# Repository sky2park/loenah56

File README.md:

# loenah56
Loenah56, A split-keyboard with 56 keys.

# How to flash firmware
Use qmk toolbox. Copy loenah folder to qmk toolbox keyboard folder.

Connect one side with bootloader mode. Execute qmk toolbox and execute below line.

qmk flash -kb loenah -km default -bl uf2-split-left (for left)

qmk flash -kb loenah -km default -bl uf2-split-right (for right)

Connect other side and do as same.

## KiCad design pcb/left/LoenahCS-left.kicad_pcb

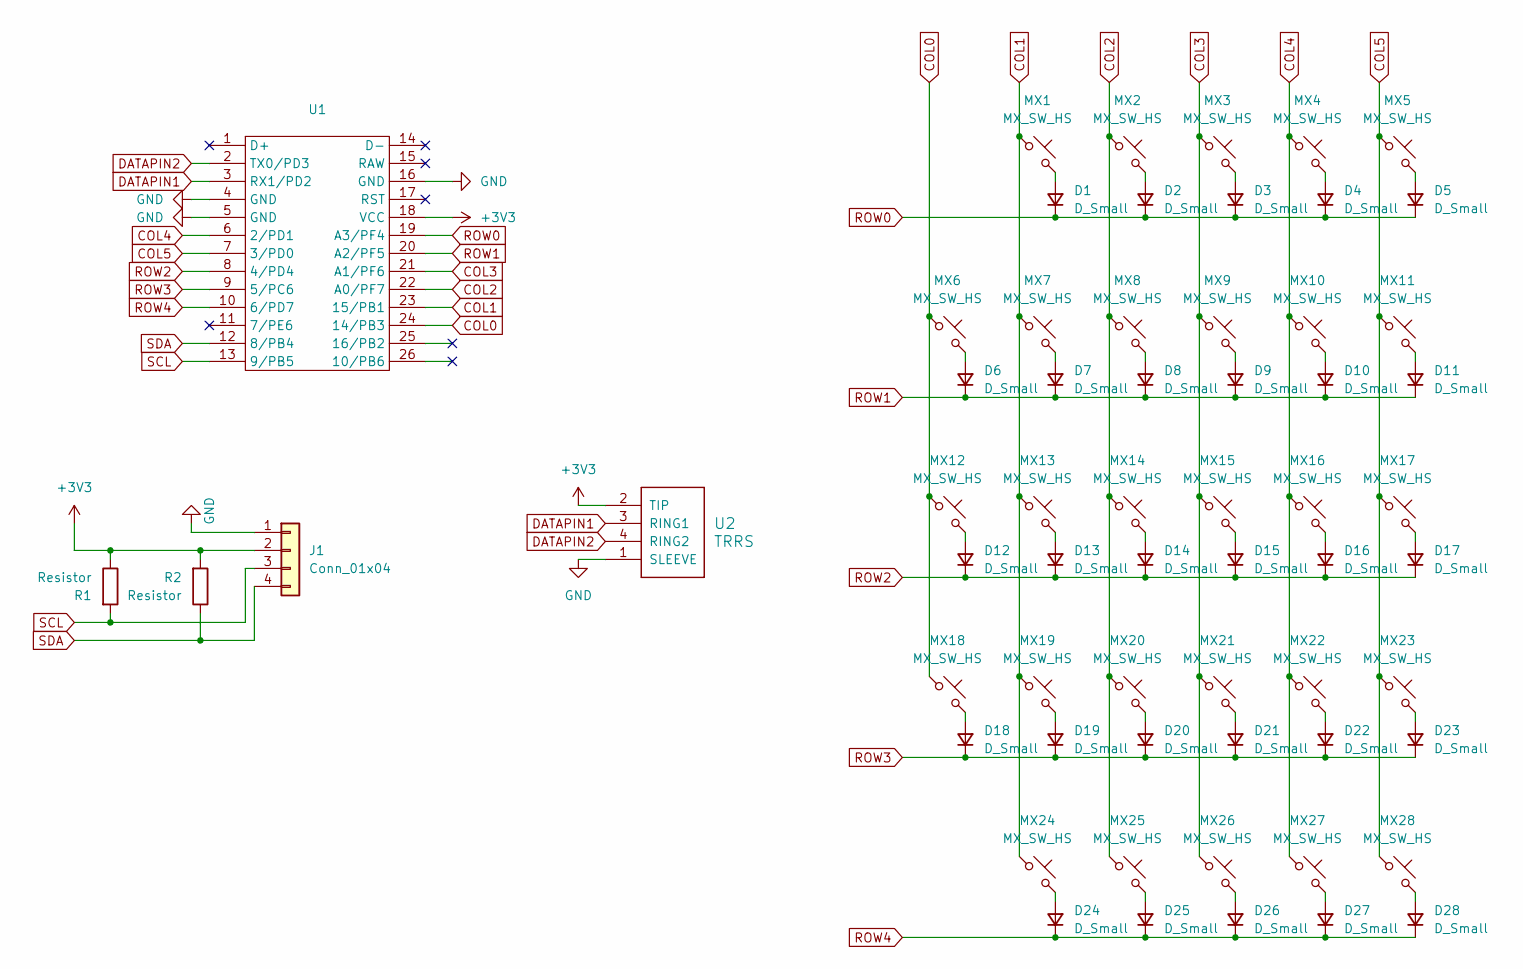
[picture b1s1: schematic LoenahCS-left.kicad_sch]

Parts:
D1, D2, D3, D4, D5, D6, D7, D8, D9, D10, D11, D12, D13, D14, D15, D16, D17, D18, D19, D20, D21, D22, D23, D24, D25, D26, D27, D28: D_Small; D_SOD-123
J1: Conn_01x04; PinHeader_1x04_P2.54mm_Vertical
MX1, MX2, MX3, MX4, MX5, MX6, MX7, MX8, MX9, MX10, MX11, MX12, MX13, MX14, MX15, MX16, MX17, MX18, MX19, MX20, MX21, MX22, MX23, MX24, MX25, MX26, MX28: MX_SW_HS; SW_MX_HS_CPG151101S11_1u
MX27: MX_SW_HS; SW_MX_HS_CPG151101S11_1.5u
R1, R2: Resistor; Resistor_0402
U1: Adafruit_KB2040
U2: TRRS; TRRS_PJ-320A

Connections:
+3V3: J1.2, R1.1, R2.2, U1.18 (VCC), U2.2 (TIP)
COL0: MX6.1, MX12.1, MX18.1, U1.24 (14/PB3)
COL1: MX1.1, MX7.1, MX13.1, MX19.1, MX24.1, U1.23 (15/PB1)
COL2: MX2.1, MX8.1, MX14.1, MX20.1, MX25.1, U1.22 (A0/PF7)
COL3: MX3.1, MX9.1, MX15.1, MX21.1, MX26.1, U1.21 (A1/PF6)
COL4: MX4.1, MX10.1, MX16.1, MX22.1, MX27.1, U1.6 (2/PD1)
COL5: MX5.1, MX11.1, MX17.1, MX23.1, MX28.1, U1.7 (3/PD0)
DATAPIN1: U1.3 (RX1/PD2), U2.3 (RING1)
DATAPIN2: U1.2 (TX0/PD3), U2.4 (RING2)
GND: J1.1, U1.4 (GND), U1.5 (GND), U1.16 (GND), U2.1 (SLEEVE)
unnamed: D1.2 (A), MX1.2
unnamed: D2.2 (A), MX2.2
unnamed: D3.2 (A), MX3.2
unnamed: D4.2 (A), MX4.2
unnamed: D5.2 (A), MX5.2
unnamed: D6.2 (A), MX6.2
unnamed: D7.2 (A), MX7.2
unnamed: D8.2 (A), MX8.2
unnamed: D9.2 (A), MX9.2
unnamed: D10.2 (A), MX10.2
unnamed: D11.2 (A), MX11.2
unnamed: D12.2 (A), MX12.2
unnamed: D13.2 (A), MX13.2
unnamed: D14.2 (A), MX14.2
unnamed: D15.2 (A), MX15.2
unnamed: D16.2 (A), MX16.2
unnamed: D17.2 (A), MX17.2
unnamed: D18.2 (A), MX18.2
unnamed: D19.2 (A), MX19.2
unnamed: D20.2 (A), MX20.2
unnamed: D21.2 (A), MX21.2
unnamed: D22.2 (A), MX22.2
unnamed: D23.2 (A), MX23.2
unnamed: D24.2 (A), MX24.2
unnamed: D25.2 (A), MX25.2
unnamed: D26.2 (A), MX26.2
unnamed: D27.2 (A), MX27.2
unnamed: D28.2 (A), MX28.2
ROW0: D1.1 (K), D2.1 (K), D3.1 (K), D4.1 (K), D5.1 (K), U1.19 (A3/PF4)
ROW1: D6.1 (K), D7.1 (K), D8.1 (K), D9.1 (K), D10.1 (K), D11.1 (K), U1.20 (A2/PF5)
ROW2: D12.1 (K), D13.1 (K), D14.1 (K), D15.1 (K), D16.1 (K), D17.1 (K), U1.8 (4/PD4)
ROW3: D18.1 (K), D19.1 (K), D20.1 (K), D21.1 (K), D22.1 (K), D23.1 (K), U1.9 (5/PC6)
ROW4: D24.1 (K), D25.1 (K), D26.1 (K), D27.1 (K), D28.1 (K), U1.10 (6/PD7)
SCL: J1.3, R1.2, U1.13 (9/PB5)
SDA: J1.4, R2.1, U1.12 (8/PB4)

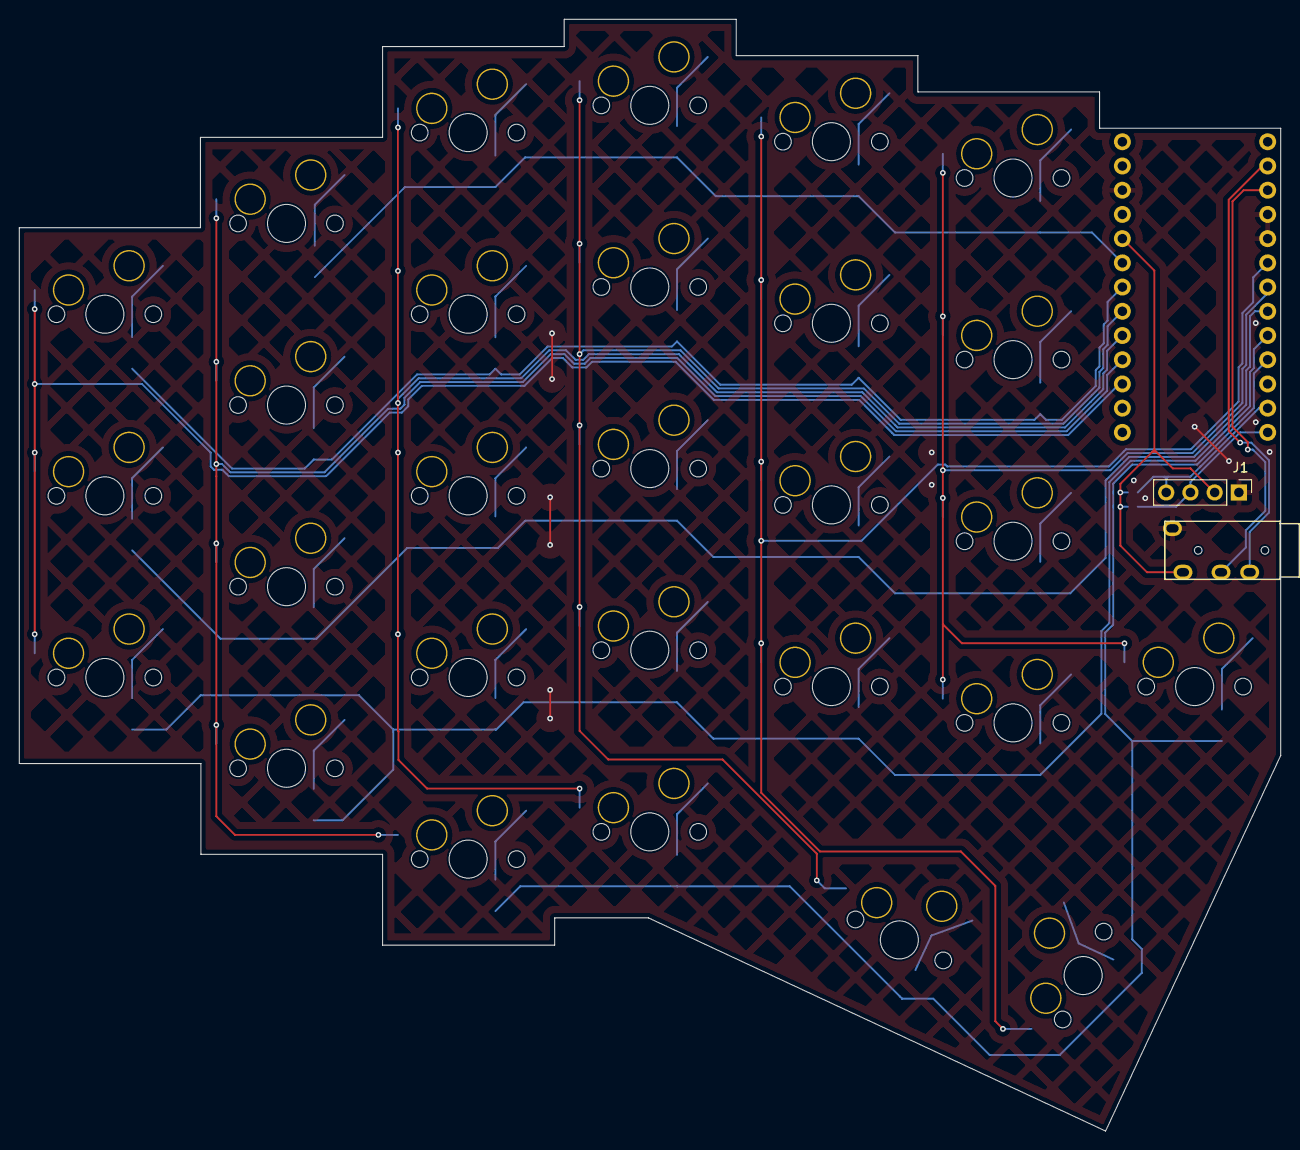
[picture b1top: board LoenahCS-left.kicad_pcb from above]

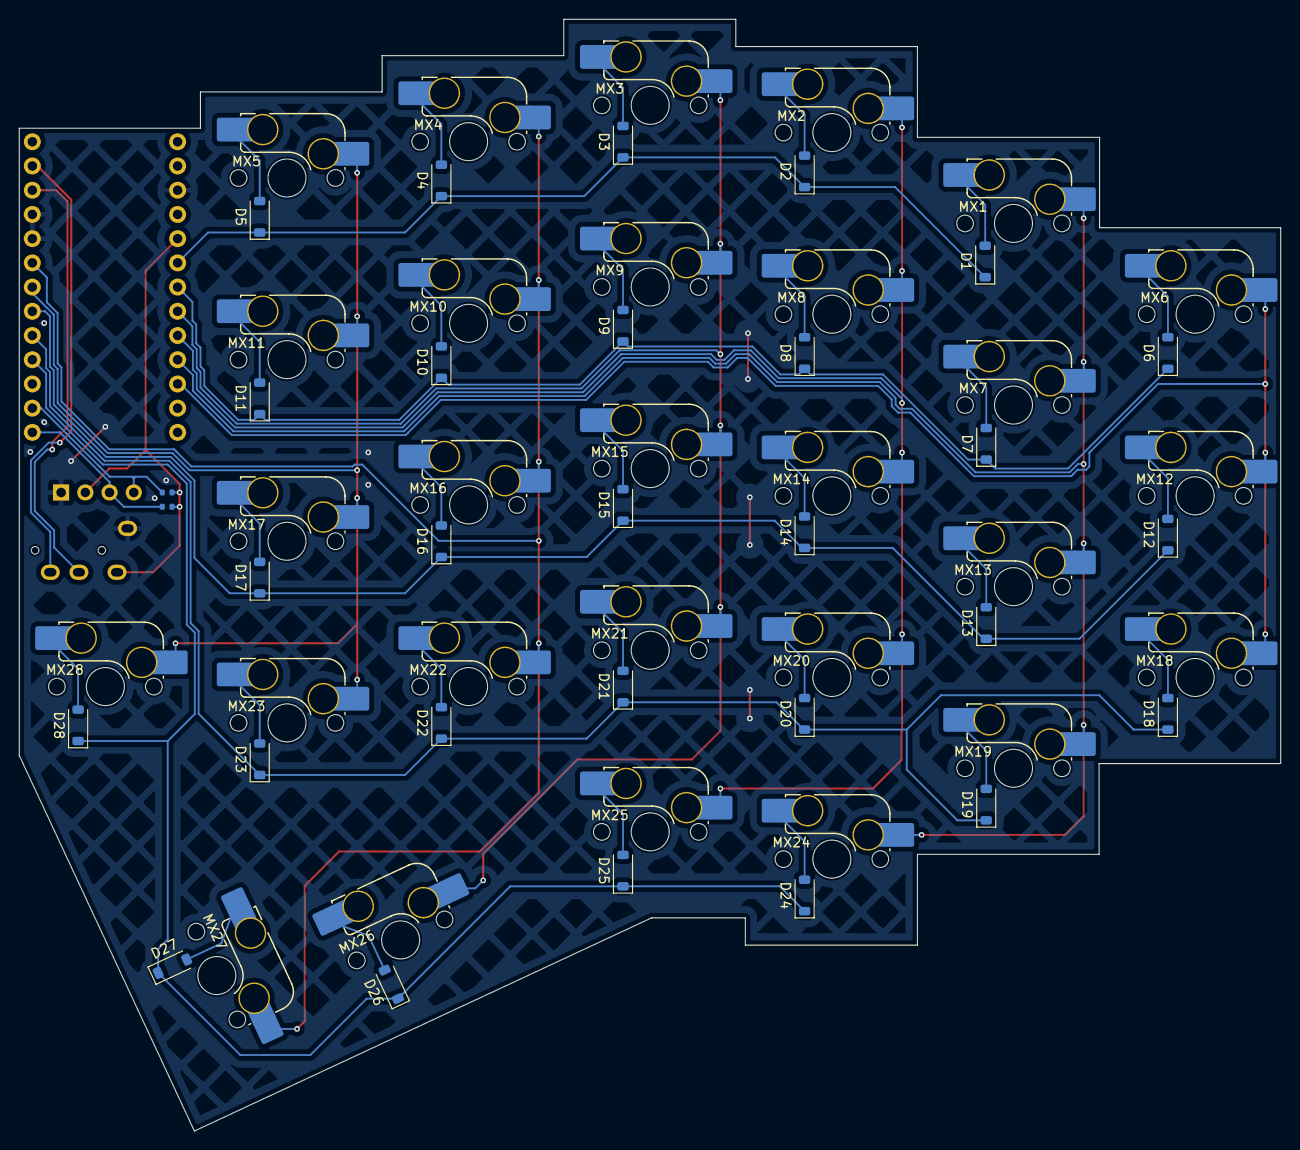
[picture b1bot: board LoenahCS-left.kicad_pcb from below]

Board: 2 copper layers, 132.3 x 116.6 mm, 61 parts (59 on the bottom side), 45 nets.

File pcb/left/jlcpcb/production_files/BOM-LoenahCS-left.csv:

Comment,Designator,Footprint,LCSC,Quantity
Resistor,"R1,R2",Resistor_0402,C25905,2
MX_SW_HS,"MX1,MX10,MX11,MX12,MX13,MX14,MX15,MX16,MX17,MX18,MX19,MX2,MX20,MX21,MX22,MX23,MX24,MX25,MX26,MX27,MX28,MX3,MX4,MX5,MX6,MX7,MX8,MX9",SW_MX_HS_CPG151101S11_1u,C41430893,28
D_Small,"D1,D10,D11,D12,D13,D14,D15,D16,D17,D18,D19,D2,D20,D21,D22,D23,D24,D25,D26,D27,D28,D3,D4,D5,D6,D7,D8,D9",D_SOD-123,C83528,28

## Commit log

2025-04-08 add files
